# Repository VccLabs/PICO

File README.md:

# PICO

This repo is still under construction, all related files will be released very soon!
<div align="center">

# PICO

### A Tiny and Powerful Arduino-Compatible Development Board for Makers

</div>

---

## Introduction

**PICO**: a tiny but powerful Arduino-compatible development board built for makers who don't want to compromise. Measuring just **17.78 × 15.24 mm (0.7" × 0.6")**, PICO is small enough to disappear into wearables, drones, and pocket-sized prototypes, yet packs enough capability to drive serious projects.

At its core, PICO runs the proven **ATmega32U4** microcontroller and exposes **14 GPIOs**, giving you plenty of room to connect sensors, displays, motors, and just about anything else you can dream up. A built-in **WS2812 addressable RGB LED** on pin D5 adds a splash of color for status indication or pure fun. The board is fully **breadboard compatible**, so you can prototype quickly without extra adapters.

PICO is **open source** by design. All schematics, PCB layouts, and source files are available in this repository, so you're free to learn from it, modify it, or build on top of it.

---

## Features

- **Ultra-compact**: 17.78 × 15.24 mm (0.7" × 0.6") footprint
- **ATmega32U4**: microcontroller with native USB
- **14 GPIOs**: including PWM, ADC, I²C, SPI, and UART
- **Built-in WS2812 RGB LED**: (addressable, on pin D5)
- **Breadboard friendly**: castellated pins
- **Multiple power options**: USB and VIN
- **Arduino IDE compatible**: program it like any Arduino Leonardo
- **Fully open source**: schematics, PCB, and code freely available

---

## Specifications

| Category | Specification |
|---|---|
| **Microcontroller** | ATmega32U4 |
| **Architecture** | 8-bit AVR |
| **Clock Speed** | 16 MHz |
| **Flash Memory** | 32 KB (4 KB used by bootloader) |
| **SRAM** | 2.5 KB |
| **EEPROM** | 1 KB |
| **GPIO Pins** | 14 <!-- TODO: confirm digital vs analog split --> |
| **PWM Channels** | 3 (D4 D10 D11) |
| **Analog Inputs** | 5 (D4 D12 A0 A1 A2) |
| **Communication** | USB, I²C, SPI, UART |
| **Operating Voltage** | 5 V |
| **Input Voltage (VIN)** | 7V~15V or power from USB port |
| **DC Current per I/O Pin** | 40mA |
| **Onboard LED** | 1× WS2812 addressable RGB (1 × 1 mm) on D5 |
| **USB Connector** | USB Type-C (**Use USB Typ-A to Type-C cable, I forgot to add the 5.1K resistord on CC pins 🐸**) |
| **Dimensions** | 17.78 × 15.24 mm (0.7" × 0.6") |
| **Weight** | ~1.1 g |

---

## Pinout

<div align="center">

</div>

| Pin   | Type           | Alternate Functions          | Notes                          |
|-------|----------------|------------------------------|--------------------------------|
| Vin   | Power (input)  | —                            | 7–15 V external supply         |
| +5V   | Power (output) | —                            | Regulated 5 V output           |
| GND   | Ground         | —                            | Common ground                  |
| RST   | Reset          | —                            | Active low; pull to GND to reset |
| SCK   | Digital        | D15, SPI Clock               | SPI bus                        |
| MOSI  | Digital        | D16, SPI Master-Out          | SPI bus                        |
| MISO  | Digital        | D17, SPI Master-In           | SPI bus                        |
| D4    | Digital        | A6 (Analog In)               | ADC capable                    |
| D3 ~  | Digital        | PWM                          | PWM output                     |
| D2    | Digital        | —                            | General-purpose I/O            |
| D0    | Digital        | RX (UART)                    | Serial receive                 |
| D1    | Digital        | TX (UART)                    | Serial transmit                |
| A0    | Analog         | Digital I/O                  | ADC input                      |
| A1    | Analog         | Digital I/O                  | ADC input                      |
| A2    | Analog         | Digital I/O                  | ADC input                      |
| D9 ~  | Digital        | PWM                          | PWM output                     |
| D10 ~ | Digital        | PWM                          | PWM output                     |
| D11 ~ | Digital        | PWM                          | PWM output                     |
| D5    | Digital        | WS2812 RGB LED (onboard)     | Connected to onboard RGB LED   |

---

## Getting Started

### 1. Install the Arduino IDE

Download and install the latest **[Arduino IDE](https://www.arduino.cc/en/software)** (version 2.x recommended).

### 2. Add the PICO Board

<!-- TODO: confirm — does PICO work out-of-the-box as "Arduino Leonardo", or do you provide a custom board package? -->

In Arduino IDE, go to **Tools → Board → Board Manager** and select **Arduino Leonardo**, PICO is fully Leonardo-compatible.

### 3. Connect PICO

Plug PICO into your computer using a USB cable (**Use USB Typ-A to Type-C cable, I forgot to add the 5.1K resistord on CC pins 🐸**). The onboard RGB LED will light up briefly to confirm power.

###  Using FastLED

If you prefer **[FastLED](https://github.com/FastLED/FastLED)** over Adafruit NeoPixel, PICO works just as well with it. FastLED is a powerful, performance-focused library with built-in color palettes, HSV support, and smooth animation helpers.

### Install FastLED

In the Arduino IDE, go to **Sketch → Include Library → Manage Libraries…**, search for **FastLED**, and click **Install**.

### 4. Upload Your First Sketch

**Blink LED using FastLED library (Example from the library itself, don't forget to change the Data pin to D5):**

```cpp
#include <Arduino.h>
#include <FastLED.h>

// How many leds do we have?
#define NUM_LEDS 1

#define DATA_PIN 5 // LED pin
#define CLOCK_PIN 13

// Define the array of leds
CRGB leds[NUM_LEDS];

void setup() { 
    //Serial.begin(9600);
    //Serial.println("BLINK setup starting");

    FastLED.addLeds<NEOPIXEL, DATA_PIN>(leds, NUM_LEDS); 
}

void loop() { 
  //Serial.println("BLINK");
  
  // Turn the LED on, then pause
  leds[0] = CRGB::Red;
  FastLED.show();
  delay(500);
  
  // Now turn the LED off, then pause
  leds[0] = CRGB::Black;
  FastLED.show();
  delay(500);
}
```

Click **Upload** — and you're up and running. 

---

## Hardware

All hardware design files are open and available in the [`/hardware`](hardware) folder:

- **Schematics** — `hardware/PICO V1.0.pdf.pdf`
- **PCB Files** — `hardware/pcb/` (Eagle source files)

> Designed in **Eagle**. Feel free to fork and remix.

---

## Onboard RGB LED

PICO features a single **WS2812B addressable RGB LED** connected to **digital pin D5**. Use the [Adafruit NeoPixel](https://github.com/adafruit/Adafruit_NeoPixel) or [FastLED](https://github.com/FastLED/FastLED) libraries to control it.

See [`examples/01_Blink_RGB`](examples/01_Blink_RGB) for a minimal working sketch.

---

## Powering PICO

PICO can be powered in two ways:

| Source | Voltage | Notes |
|--------|---------|-------|
| **USB** | 5 V | Plug-and-play for programming and power |
| **VIN pin** | 7V~15V | For battery or external supply |

> ⚠️ Do **not** apply power to USB and VIN simultaneously unless you understand the implications.

---

##  Community & Support

Got questions, ideas, or want to share what you built with PICO?

-  **Discussions**: [GitHub Discussions](https://github.com/VccLabs/PICO/discussions)
-  **Issues / Bugs**: [Open an issue](https://github.com/VccLabs/PICO/issues)
-  **Website**: [vcclabs.com](https://vcclabs.com)
-  **Email**: thevcclabs@gmail.com

---

## Contributing

Contributions are welcome! Whether it's a bug fix, a new example sketch, or documentation improvements, feel free to open a pull request.

---

## License

- **Software & examples** are licensed under the [MIT License](LICENSE).
- **Hardware design files** are licensed under the [Creative Commons Attribution 4.0 International License (CC BY 4.0)](https://creativecommons.org/licenses/by/4.0/).

You are free to use, modify, and distribute - including for commercial purposes - provided you credit **Vcc Labs** as the original creator.

---
https://github.com/fastled/fastled
## 🙏 Acknowledgments

PICO was made possible thanks to:

- The **78 backers** who supported us on [Kickstarter](https://www.kickstarter.com/projects/vcclabs/pico-a-tiny-and-powerful-development-board-for-makers) 🚀
- The open-source hardware community
- The [Arduino](https://arduino.cc), [Sparkfun](https://sparkfun.com), [FastLED](https://github.com/fastled/fastled), and [Adafruit](https://adafruit.com) teams for their incredible libraries and tools

---

<div align="center">

**Built with ❤️ by [Vcc Labs](https://vcclabs.com)**

</div>

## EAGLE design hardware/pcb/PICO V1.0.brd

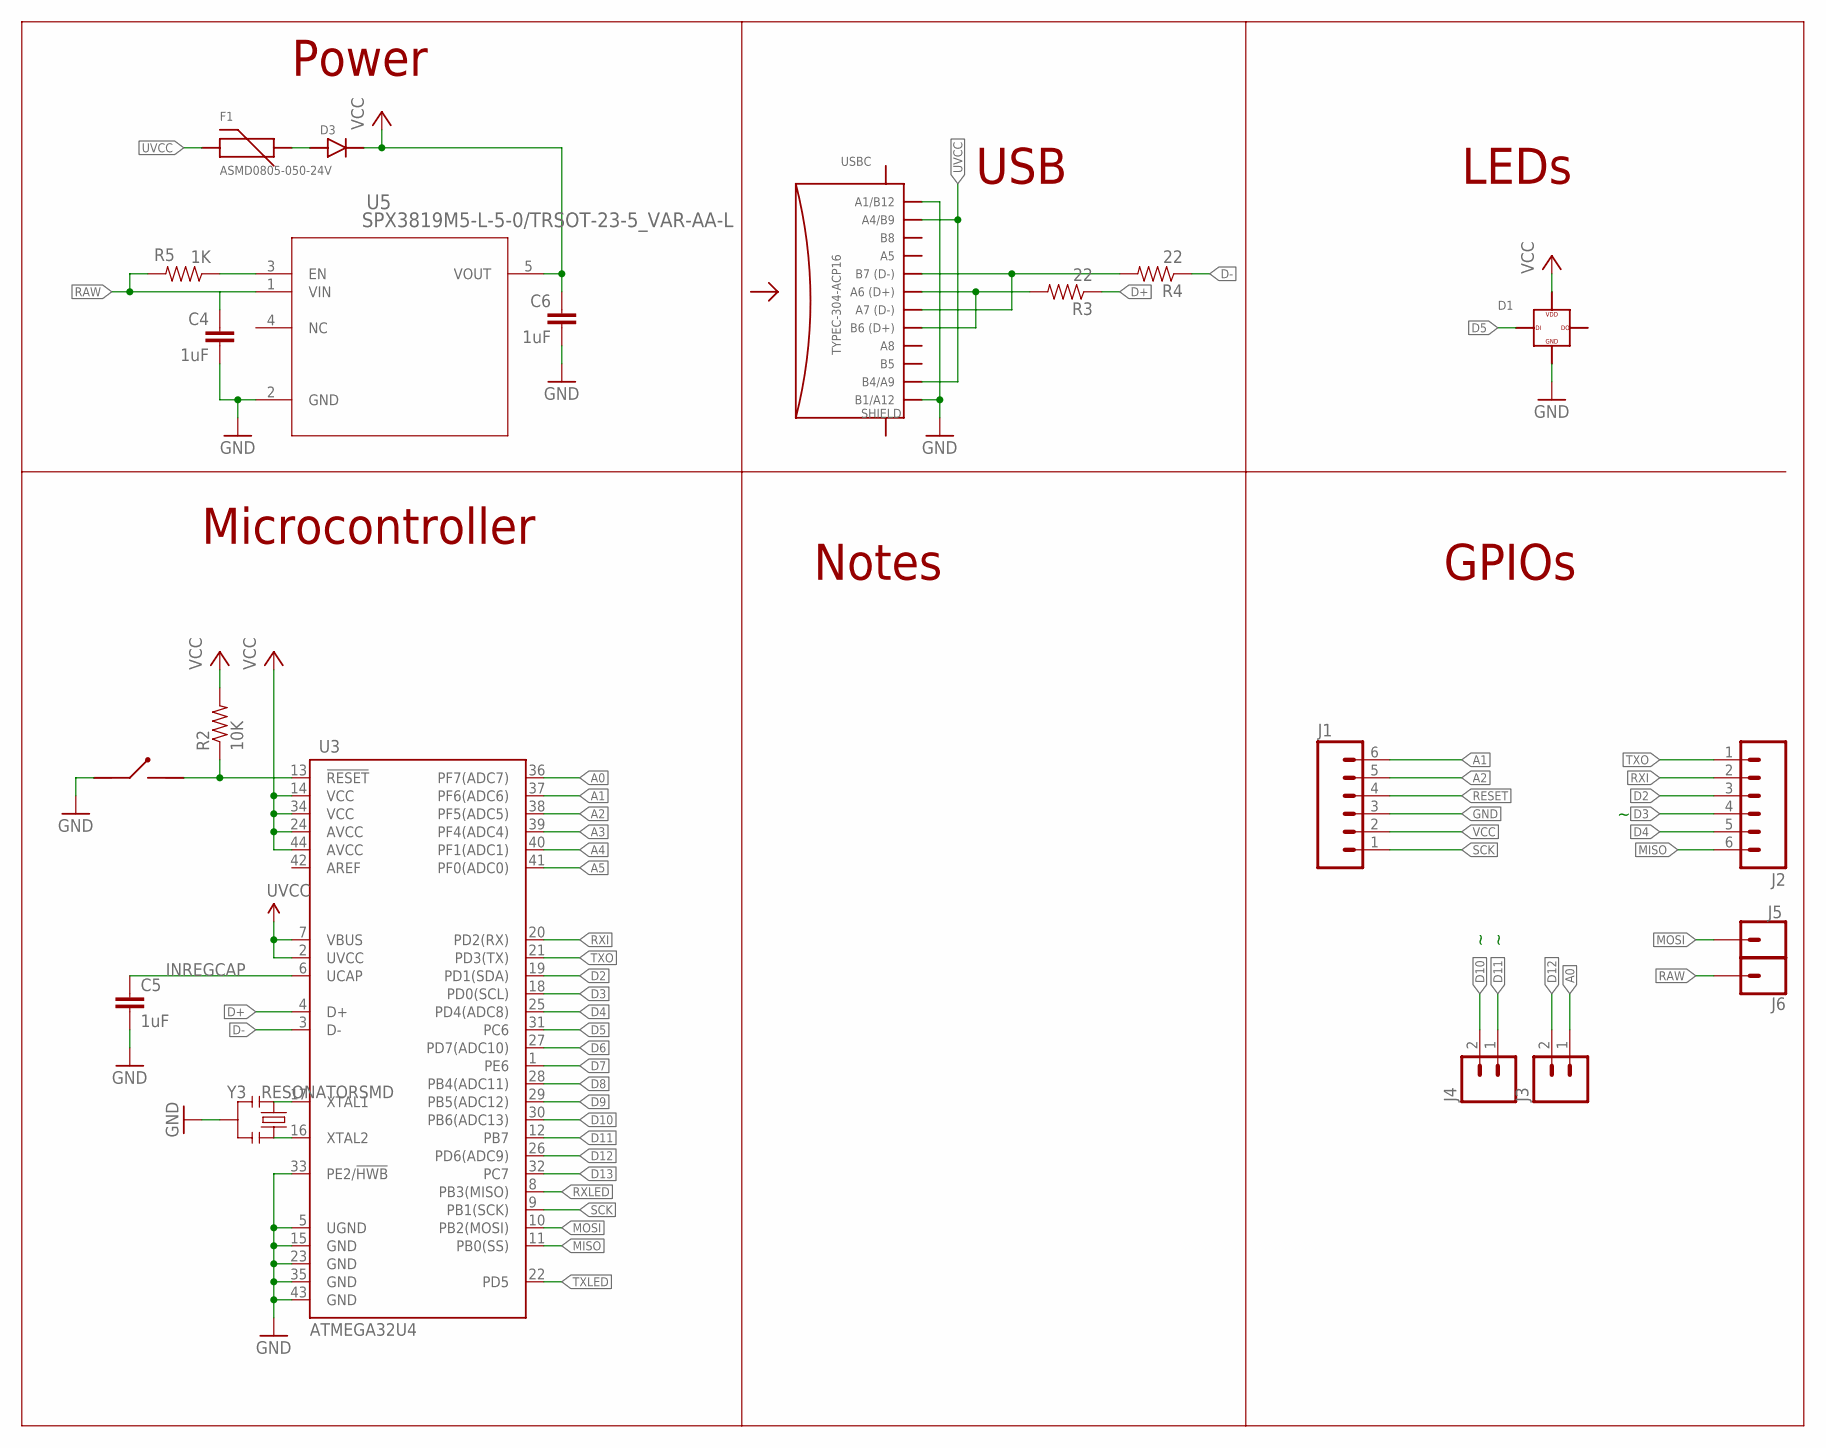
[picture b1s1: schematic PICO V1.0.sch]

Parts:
C4, C5, C6: 1uF; 0402-CAP
D1: XL-1010RGBC-WS2812B
D3: 1N4148W-TP
F1: ASMD0805-050-24V
J1, J2: M06SILK_FEMALE_PTH; 1X06
J3, J4: M02PTH; 1X02
J5, J6: CONN_01; 1X01
R2: 10K; 0402-RES
R3, R4: 22; 0402-RES
R5: 1K; 0402-RES
S1: B3U-1000P
U3: ATMEGA32U4; QFN-44-NOPAD_1:1-OUTFAKES
U5: SPX3819M5-L-5-0/TRSOT-23-5_VAR-AA-L; TPSPX3819M5-L-5-0/3
USBC: TYPEC-304-ACP16
Y3: RESONATORSMD; RESONATOR-SMD

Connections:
A0: J3.1, U3.36 (PF7(ADC7))
A1: J1.6, U3.37 (PF6(ADC6))
A2: J1.5, U3.38 (PF5(ADC5))
A3: U3.39 (PF4(ADC4))
A4: U3.40 (PF1(ADC1))
A5: U3.41 (PF0(ADC0))
D2: J2.3, U3.19 (PD1(SDA))
D3: J2.4, U3.18 (PD0(SCL))
D4: J2.5, U3.25 (PD4(ADC8))
D5: D1.4, U3.31 (PC6)
D6: U3.27 (PD7(ADC10))
D7: U3.1 (PE6)
D8: U3.28 (PB4(ADC11))
D9: U3.29 (PB5(ADC12))
D10: J4.2, U3.30 (PB6(ADC13))
D11: J4.1, U3.12 (PB7)
D12: J3.2, U3.26 (PD6(ADC9))
D13: U3.32 (PC7)
D+: R3.1, U3.4 (D+)
D-: R4.1, U3.3 (D-)
GND: C4.2, C5.2, C6.2, D1.3, J1.3, S1.1, U3.5 (UGND), U3.15 (GND), U3.23 (GND), U3.33 (PE2/!HWB), U3.35 (GND), U3.43 (GND), U5.2 (GND), USBC.A1/B12, USBC.B1/A12, Y3.2
INREGCAP: C5.1, U3.6 (UCAP)
MISO: J2.6, U3.11 (PB0(SS))
MOSI: J5.1, U3.10 (PB2(MOSI))
unnamed: U3.16 (XTAL2), Y3.3
unnamed: U3.17 (XTAL1), Y3.1
unnamed: R5.1, U5.3 (EN)
unnamed: D3.1, F1.2
unnamed: R3.2, USBC.A6, USBC.B6
unnamed: R4.2, USBC.A7, USBC.B7
RAW: C4.1, J6.1, R5.2, U5.1 (VIN)
RESET: J1.4, R2.1, S1.2, U3.13 (!RESET)
RXI: J2.2, U3.20 (PD2(RX))
RXLED: U3.8 (PB3(MISO))
SCK: J1.1, U3.9 (PB1(SCK))
TXLED: U3.22 (PD5)
TXO: J2.1, U3.21 (PD3(TX))
UVCC: F1.1, U3.2 (UVCC), U3.7 (VBUS), USBC.A4/B9, USBC.B4/A9
VCC: C6.1, D1.2, D3.2, J1.2, R2.2, U3.14 (VCC), U3.24 (AVCC), U3.34 (VCC), U3.44 (AVCC), U5.5 (VOUT)

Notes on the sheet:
Power
USB
LEDs
Microcontroller
GPIOs
Notes

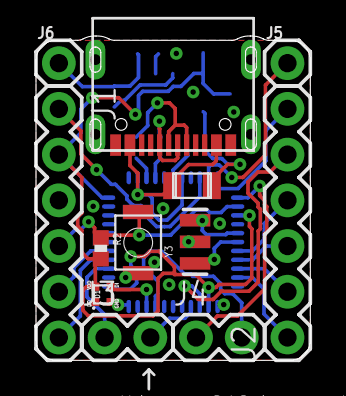
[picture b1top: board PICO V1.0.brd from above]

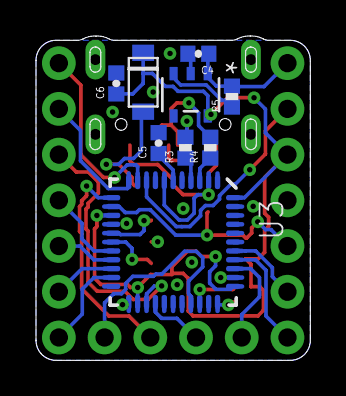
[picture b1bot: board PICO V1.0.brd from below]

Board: 2 copper layers, 15.2 x 18.0 mm, 21 parts (9 on the bottom side), 29 nets.

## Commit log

2026-05-14 Add full README with specs, source files, pinout, and FastLED guide
2026-05-14 Remove desktop.ini files and ignore them
2026-05-14 Properly ignore desktop.ini files
2026-05-14 Pushing Blink example

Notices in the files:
README.md:
License: MIT
Hardware: CC BY 4.0
parts and their libraries:
SparkFun-Capacitors: Licensing: Creative Commons ShareAlike 4.0 International - https://creativecommons.org/licenses/by-sa/4.0
COPYRIGHT: Copyright (C) 2024 Ultra Librarian. All rights reserved.
